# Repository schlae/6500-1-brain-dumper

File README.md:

# 6500/1 Brain Dumper

Do you have a 6500/1 microcontroller made by MOS, Rockwell, or NCR? (and possibly others)
Do you want to dump the contents of the ROM? Here's a board for you!

This design is derived from work by Jim Brain documented [here](https://e4aws.silverdr.com/hacks/6500_1/)
with design files [here](https://github.com/Project-64/reloaded/tree/master/1520/extraction).

The original design was built on a breadboard. I've turned this into a simple PC board to save
you the effort of wiring it up. Along the way, I ported the code to another MCU (ATmega644) mostly
because that is what I had. I also edited the code to make it slightly more reliable by putting out
more clock cycles while RESET# is held low. (Although it is still not perfect and it usually takes
several tries to get a good dump.)

[Schematic](6500Dumper.pdf)

[Bill of Materials](6500Dumper.csv)

## Fabrication

I have not included the fab files because I haven't fabbed out and tested this board yet. Do this
at your own risk from the KiCad source files.

## Firmware

Build the firmware using the `make` command, assuming you have `avr-gcc` and all that installed.
I like to use the TL866 programmer with the `minipro` Linux software to program the ATmega.

Make sure to set the configuration fuses as follows:

* fuses\_lo = 0xff
* fuses\_hi = 0xd9
* fuses\_ext = 0xfd
* lock = 0xff

## Usage

The device works by putting the 6500/1 into test mode by applying 10V to the RESET# input. It
then bootstraps a small program into the MCU's RAM which copies the contents of the internal
ROM out through an I/O port, which the ATmega can read and route through its serial port to
the host.

After building up the board, connect a serial cable such as FTDI or a [module](https://www.sparkfun.com/products/15096).
Make sure it is configured for 5V operation! On the modules this is a little jumper or
PCB trace you have to cut and solder.

Connect an oscilloscope to the TARGET RESET test point on one channel (set to trigger on the
rising edge) and another channel to the PC1 test point (header pin 2 on J6). This will let
you tell if the 6500/1 has entered test mode and is putting out data.

Connect a 5V bench supply to the +5V and GND test points. Connect an *adjustable* bench supply
to the +10V input and GND. Set the current limit on this supply to something less than 100mA
to help prevent damage the chip under test, just in case.

If this is your first time using the board, you may want to power it up without the 6500/1
in the socket just to verify that the RESET# output behaves correctly. See the waveforms
below.

Put the 6500/1 chip into the J1 socket, and turn on the power. On the oscilloscope, you should
see the RESET# line go up to 10V, then back down to 5V, and you should see a row of pulses
on PC1. If you don't, examine the magnitude of the pulses on PC1 that occur *while RESET# is
at 10V*. Pulses that appear stunted or at around 2.5V mean that there is output contention
and the 6500/1 is not in test mode. 

**Note that CH4 (PC1) has two stunted pulses caused by output contention. CH1=reset and CH2=clock**

You might have to increase the +10V rail (but keep it below
12V or so) and then hit the reset button on the upper left to try again. It may take several tries.

If all goes well, you should see a regular set of pulses on PC1, something like this:

**CH4 (PC1) shows regular pulses after RESET# falls to 5V.**

If that is the case, binary data will be transmitted from the ATmega at 57600 baud, 8N1.
This represents the binary data read back from the 6500/1's ROM (located at address
0x800 to 0xfff). I've provided a terrible Python program, `ser_read.py` to save that to
a file. You'll want to edit it to change the filename, serial port, etc (I told you
it's bad!)

## Licensing

This program is free software; you can redistribute it and/or modify
it under the terms of the GNU General Public License as published by
the Free Software Foundation; either version 2 of the License, or
(at your option) any later version.

This program is distributed in the hope that it will be useful,
but WITHOUT ANY WARRANTY; without even the implied warranty of
MERCHANTABILITY or FITNESS FOR A PARTICULAR PURPOSE.  See the
GNU General Public License for more details.

You should have received a copy of the GNU General Public License
along with this program; if not, write to the Free Software
Foundation, Inc., 59 Temple Place, Suite 330, Boston, MA  02111-1307  USA

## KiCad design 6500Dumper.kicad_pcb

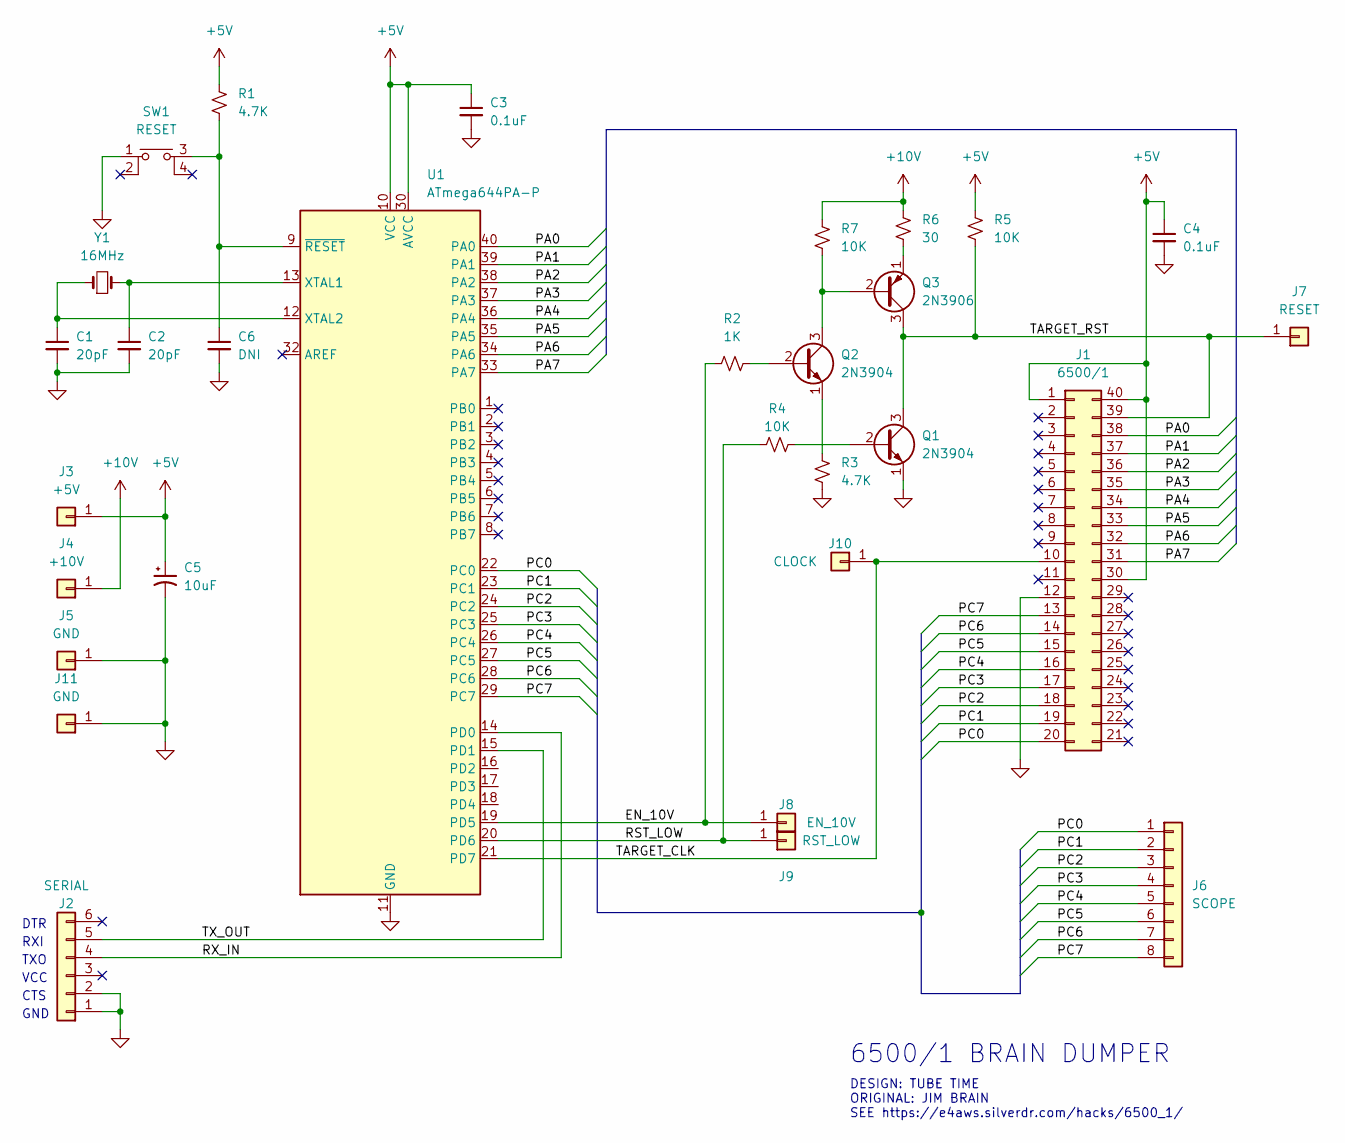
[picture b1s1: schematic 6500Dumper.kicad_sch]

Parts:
C1, C2: 20pF; C_Disc_D3.0mm_W1.6mm_P2.50mm
C3, C4: 0.1uF; CAPAC200
C5: 10uF; CAPAE200P500X1100
C6: DNI; C_Disc_D3.0mm_W1.6mm_P2.50mm
J1: 6500/1; DIP254P1524X635-40
J2: SERIAL; PinHeader_1x06_P2.54mm_Horizontal
J3: +5V; TP_KEYSTONE_5005_9
J4: +10V; TP_KEYSTONE_5005_9
J5, J11: GND; TP_KEYSTONE_5005_9
J6: SCOPE; PinHeader_1x08_P2.54mm_Vertical
J7: RESET; TP_KEYSTONE_5005_9
J8: EN_10V; TP_KEYSTONE_5005_9
J9: RST_LOW; TP_KEYSTONE_5005_9
J10: CLOCK; TP_KEYSTONE_5005_9
Q1, Q2: 2N3904; TO-92L
Q3: 2N3906; TO-92L
R1, R3: 4.7K; RESA500
R2: 1K; RESA500
R4, R5, R7: 10K; RESA500
R6: 30; RESA500
SW1: RESET; ESWITCH_TL1105
U1: ATmega644PA-P; DIP254P1524X635-40
Y1: 16MHz; Crystal_HC49-U_Vertical

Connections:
+5V: C3.1, C4.1, C5.1, J1.1, J1.30, J1.40, J3.1, R1.1, R5.1, U1.10 (VCC), U1.30 (AVCC)
+10V: J4.1, R6.1, R7.1
/EN_10V: J8.1, R2.1, U1.19 (PD5)
/PA0: J1.38, U1.40 (PA0)
/PA1: J1.37, U1.39 (PA1)
/PA2: J1.36, U1.38 (PA2)
/PA3: J1.35, U1.37 (PA3)
/PA4: J1.34, U1.36 (PA4)
/PA5: J1.33, U1.35 (PA5)
/PA6: J1.32, U1.34 (PA6)
/PA7: J1.31, U1.33 (PA7)
/PC0: J1.20, J6.1, U1.22 (PC0)
/PC1: J1.19, J6.2, U1.23 (PC1)
/PC2: J1.18, J6.3, U1.24 (PC2)
/PC3: J1.17, J6.4, U1.25 (PC3)
/PC4: J1.16, J6.5, U1.26 (PC4)
/PC5: J1.15, J6.6, U1.27 (PC5)
/PC6: J1.14, J6.7, U1.28 (PC6)
/PC7: J1.13, J6.8, U1.29 (PC7)
/RST_LOW: J9.1, R4.1, U1.20 (PD6)
/RX_IN: J2.4, U1.14 (PD0)
/TARGET_CLK: J1.10, J10.1, U1.21 (PD7)
/TARGET_RST: J1.39, J7.1, Q1.3 (C), Q3.3 (C), R5.2
/TX_OUT: J2.5, U1.15 (PD1)
GND: C1.2, C2.2, C3.2, C4.2, C5.2, C6.2, J1.12, J2.1, J2.2, J5.1, J11.1, Q1.1 (E), R3.2, SW1.1, U1.11 (GND), U1.31 (GND)
unnamed: Q1.2 (B), R4.2
unnamed: Q2.2 (B), R2.2
unnamed: Q2.3 (C), Q3.2 (B), R7.2
unnamed: Q2.1 (E), R3.1
unnamed: Q3.1 (E), R6.2
unnamed: C2.1, U1.13 (XTAL1), Y1.2
unnamed: C1.1, U1.12 (XTAL2), Y1.1
unnamed: C6.1, R1.2, SW1.3, U1.9 (~RESET)

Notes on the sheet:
TXO
VCC
DESIGN: TUBE TIME ORIGINAL: JIM BRAIN SEE https://e4aws.silverdr.com/hacks/6500_1/
6500/1 BRAIN DUMPER
GND
CTS
DTR
RXI

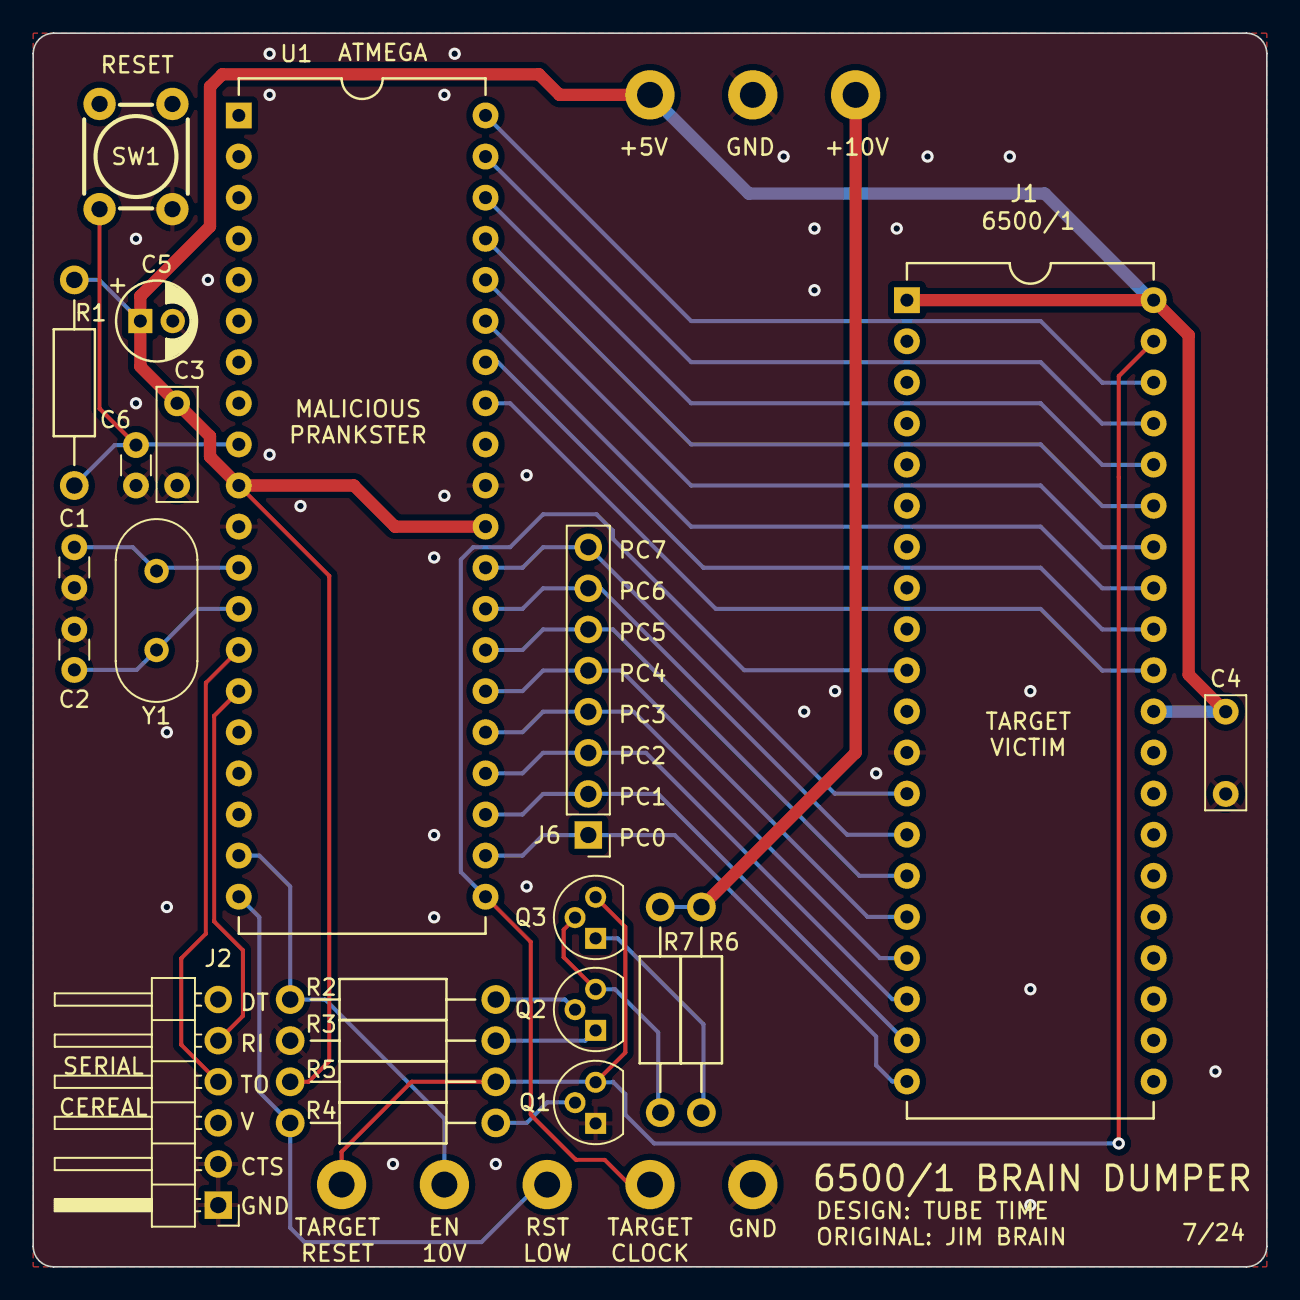
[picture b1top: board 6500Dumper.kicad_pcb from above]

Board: 2 copper layers, 76.2 x 76.2 mm, 30 parts (0 on the bottom side), 33 nets.
